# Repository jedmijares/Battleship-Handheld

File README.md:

# Battleship Handheld

This project was created as the final project for EE 287 (Intro to Embedded Systems), by Jed Mijares and Jacob Culler.

## YouTube Video Demo

[Watch Here](https://www.youtube.com/watch?v=jDSAx5fQOlo)

## Compiling

Battleship was written and built with Keil uVision5.

## Description and Operation

If you are not familiar with the board game Battleship, you can read about it [here.](https://en.wikipedia.org/wiki/Battleship_(game))

We implemented the game on a Texas Intrument Tiva C Series Launchpad (EK-TM4C123GXL). When booted up, a short credit message is displayed on a Nokia 5110 screen. The user may press any button to proceed to the game board. The time at which they press the button is used as a seed for a randomization function, and we use this function to randomly place a length 2, length 3, and length 4 ship on an 8x8 grid. Next, the player will use the D-pad to navigate and the select button to fire at the selected square. The game will display an X for each square with a targeted ship and a 0 for each targeted empty square. The game is completed when the player has sunken each ship. At this point, a win screen is displayed, showing the number of shots the player had to fire to complete the game. They player can hit any button to reset the game and play again.

## Explanation of Design Choices

We were attracted to using the Nokia 5110 screen, as Dr. Valvano had provided a library for it as part of his online Embedded Systems course, which we referred to often throughout this semester. We settled upon implementing Battleship after discovering that the Nokia screen flickered a lot when sprites were quickly moved across it.

We used an 8x8 grid for the board as it fit nicely on the Nokia's 48x84 pixel screen. This left enough space for 6 rows of 4 characters, which we used to display the number of shots fired, the number of successful hits, and which ships had been successfully sunk. In software, the board is a 2 dimensional array of _Square_ structs, which keep track of whether a tile has been shot and an ID for the ship that resides there (or lack thereof).

The PCB features several extraneous components. These include a terminal block for breaking out UART pins, an extra unused button, and several rows of jumper pins. These serve no purpose in the current design, but were added in case we decided to implement a feature that would require them.

## Parts List

* TM4C123G LaunchPad Evaluation Kit
* Nokia 5110 Screen Breakout Board
* Piezo Buzzer
* 10kR Resistor (5)
* Pushbutton Switch (5)

### Optional Components

* 330R Resistor (may be used to enable the backlight)
* 4-pin terminal block (breaks out the UART pins, which currently are not used)
* 10kR Resistor (for extra button that currently serves no purpose)
* Pushbutton Switch (extra button that currently serves no purpose)

## Flow Diagram

[Code Flow Diagram](https://github.com/jedmijares/EE-287-Final-Project/blob/master/Media/Code%20Block%20Diagram.pdf)

## Explanation of Major Components

The Tiva board is crucial to the project, and controls all the other components and handles the processing for the game itself.

The Tiva communicates with the Nokia 5110 screen serially and uses it to communicate all visual output.

A piezo buzzer is also implemented. Whenever a button is pressed, the SysTick timer is used to oscillate the buzzer pin for a specified number of milliseconds.

The PCB was designed in Autodesk EAGLE. Relevant design files are in the EAGLE folder.

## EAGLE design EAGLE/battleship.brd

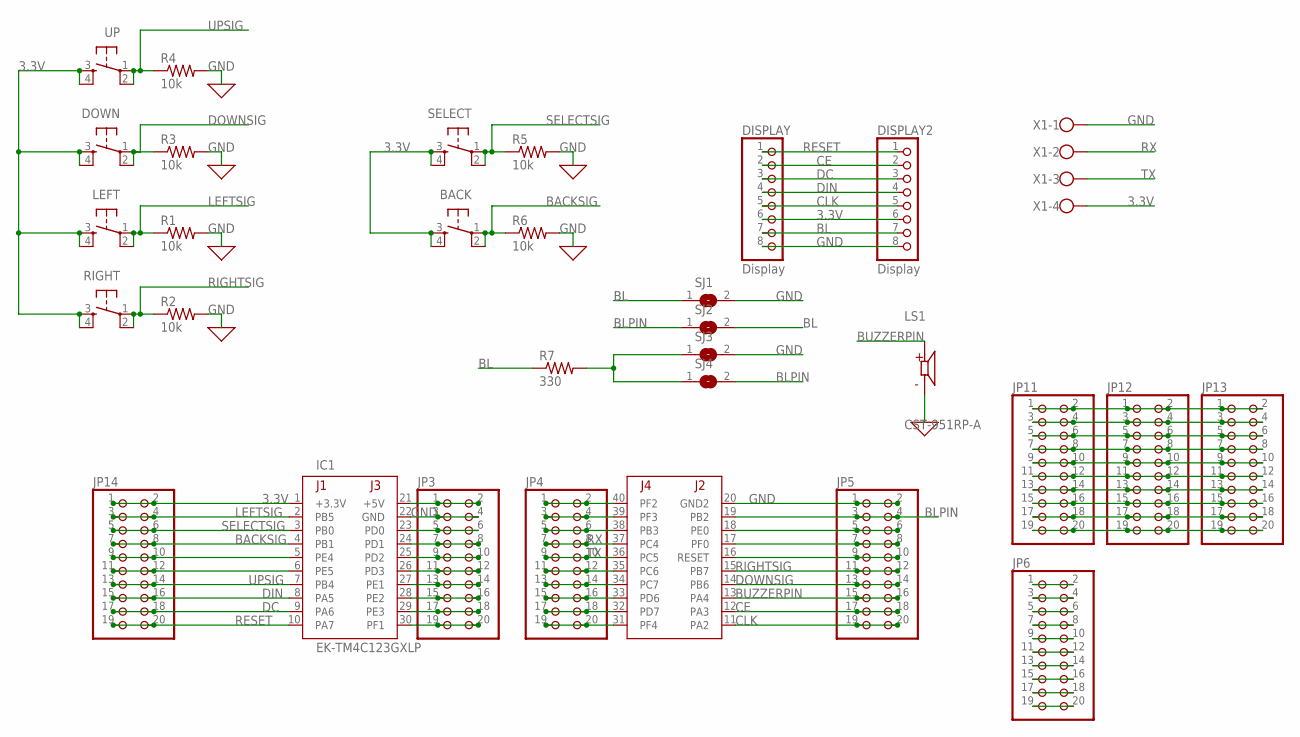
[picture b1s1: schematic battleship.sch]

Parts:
BACK: TAC_SWITCHPTH; TACTILE-PTH
DISPLAY, DISPLAY2: Display; 1X08
DOWN: TAC_SWITCHPTH; TACTILE-PTH
IC1: EK-TM4C123GXLP; TM4C123LAUNCHPAD
JP3, JP4, JP5, JP6, JP11, JP12, JP13, JP14: PINHD-2X10; 2X10
LEFT: TAC_SWITCHPTH; TACTILE-PTH
LS1: CST-951RP-A; CUI_CST-951RP-A
R1, R2, R3, R4, R5, R6: 10k; 0207/10
R7: 330; 0207/10
RIGHT: TAC_SWITCHPTH; TACTILE-PTH
SELECT: TAC_SWITCHPTH; TACTILE-PTH
SJ1, SJ2, SJ3, SJ4: SJ
UP: TAC_SWITCHPTH; TACTILE-PTH
X1: W237-4

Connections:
3.3V: BACK.3, BACK.4, DISPLAY.6, DISPLAY2.6, DOWN.3, DOWN.4, IC1.1 (+3.3V), JP14.1, JP14.2, LEFT.3, LEFT.4, RIGHT.3, RIGHT.4, SELECT.3, SELECT.4, UP.3, UP.4, X1.4
BACKSIG: BACK.1, BACK.2, IC1.4 (PB1), JP14.7, JP14.8, R6.1
BL: DISPLAY.7, DISPLAY2.7, R7.1, SJ1.1, SJ2.2
BLPIN: IC1.19 (PB2), JP5.3, JP5.4, SJ2.1, SJ4.2
BUZZERPIN: IC1.13 (PA4), JP5.15, JP5.16, LS1.P
CE: DISPLAY.2, DISPLAY2.2, IC1.12 (PA3), JP5.17, JP5.18
CLK: DISPLAY.5, DISPLAY2.5, IC1.11 (PA2), JP5.19, JP5.20
DC: DISPLAY.3, DISPLAY2.3, IC1.9 (PA6), JP14.17, JP14.18
DIN: DISPLAY.4, DISPLAY2.4, IC1.8 (PA5), JP14.15, JP14.16
DOWNSIG: DOWN.1, DOWN.2, IC1.14 (PB6), JP5.13, JP5.14, R3.1
GND: DISPLAY.8, DISPLAY2.8, IC1.20 (GND2), IC1.22 (GND), JP3.3, JP3.4, JP5.1, JP5.2, LS1.M, R1.2, R2.2, R3.2, R4.2, R5.2, R6.2, SJ1.2, SJ3.2, X1.1
LEFTSIG: IC1.2 (PB5), JP14.3, JP14.4, LEFT.1, LEFT.2, R1.1
unnamed: JP6.1, JP6.2
unnamed: JP6.3, JP6.4
unnamed: JP6.5, JP6.6
unnamed: JP6.7, JP6.8
unnamed: JP6.9, JP6.10
unnamed: R7.2, SJ3.1, SJ4.1
unnamed: JP6.11, JP6.12
unnamed: JP6.13, JP6.14
unnamed: JP6.15, JP6.16
unnamed: JP6.19, JP6.20
unnamed: JP6.17, JP6.18
unnamed: IC1.5 (PE4), JP14.9, JP14.10
unnamed: IC1.21 (+5V), JP3.1, JP3.2
unnamed: IC1.23 (PD0), JP3.5, JP3.6
unnamed: IC1.24 (PD1), JP3.7, JP3.8
unnamed: IC1.16 (RESET), JP5.9, JP5.10
unnamed: IC1.17 (PF0), JP5.7, JP5.8
unnamed: IC1.18 (PE0), JP5.5, JP5.6
unnamed: IC1.28 (PE2), JP3.15, JP3.16
unnamed: IC1.29 (PE3), JP3.17, JP3.18
unnamed: IC1.30 (PF1), JP3.19, JP3.20
unnamed: IC1.31 (PF4), JP4.19, JP4.20
unnamed: IC1.32 (PD7), JP4.17, JP4.18
unnamed: IC1.26 (PD3), JP3.11, JP3.12
unnamed: IC1.25 (PD2), JP3.9, JP3.10
unnamed: JP11.3, JP11.4, JP12.3, JP12.4, JP13.3, JP13.4
unnamed: JP11.7, JP11.8, JP12.7, JP12.8, JP13.7, JP13.8
unnamed: IC1.33 (PD6), JP4.15, JP4.16
unnamed: IC1.34 (PC7), JP4.13, JP4.14
unnamed: JP11.11, JP11.12, JP12.11, JP12.12, JP13.11, JP13.12
unnamed: IC1.35 (PC6), JP4.11, JP4.12
unnamed: JP11.15, JP11.16, JP12.15, JP12.16, JP13.15, JP13.16
unnamed: JP11.17, JP11.18, JP12.17, JP12.18, JP13.17, JP13.18
unnamed: JP11.19, JP11.20, JP12.19, JP12.20, JP13.19, JP13.20
unnamed: IC1.38 (PB3), JP4.5, JP4.6
unnamed: IC1.39 (PF3), JP4.3, JP4.4
unnamed: IC1.40 (PF2), JP4.1, JP4.2
unnamed: IC1.6 (PE5), JP14.11, JP14.12
unnamed: IC1.27 (PE1), JP3.13, JP3.14
unnamed: JP11.1, JP11.2, JP12.1, JP12.2, JP13.1, JP13.2
unnamed: JP11.5, JP11.6, JP12.5, JP12.6, JP13.5, JP13.6
unnamed: JP11.9, JP11.10, JP12.9, JP12.10, JP13.9, JP13.10
unnamed: JP11.13, JP11.14, JP12.13, JP12.14, JP13.13, JP13.14
RESET: DISPLAY.1, DISPLAY2.1, IC1.10 (PA7), JP14.19, JP14.20
RIGHTSIG: IC1.15 (PB7), JP5.11, JP5.12, R2.1, RIGHT.1, RIGHT.2
RX: IC1.37 (PC4), JP4.7, JP4.8, X1.2
SELECTSIG: IC1.3 (PB0), JP14.5, JP14.6, R5.1, SELECT.1, SELECT.2
TX: IC1.36 (PC5), JP4.9, JP4.10, X1.3
UPSIG: IC1.7 (PB4), JP14.13, JP14.14, R4.1, UP.1, UP.2

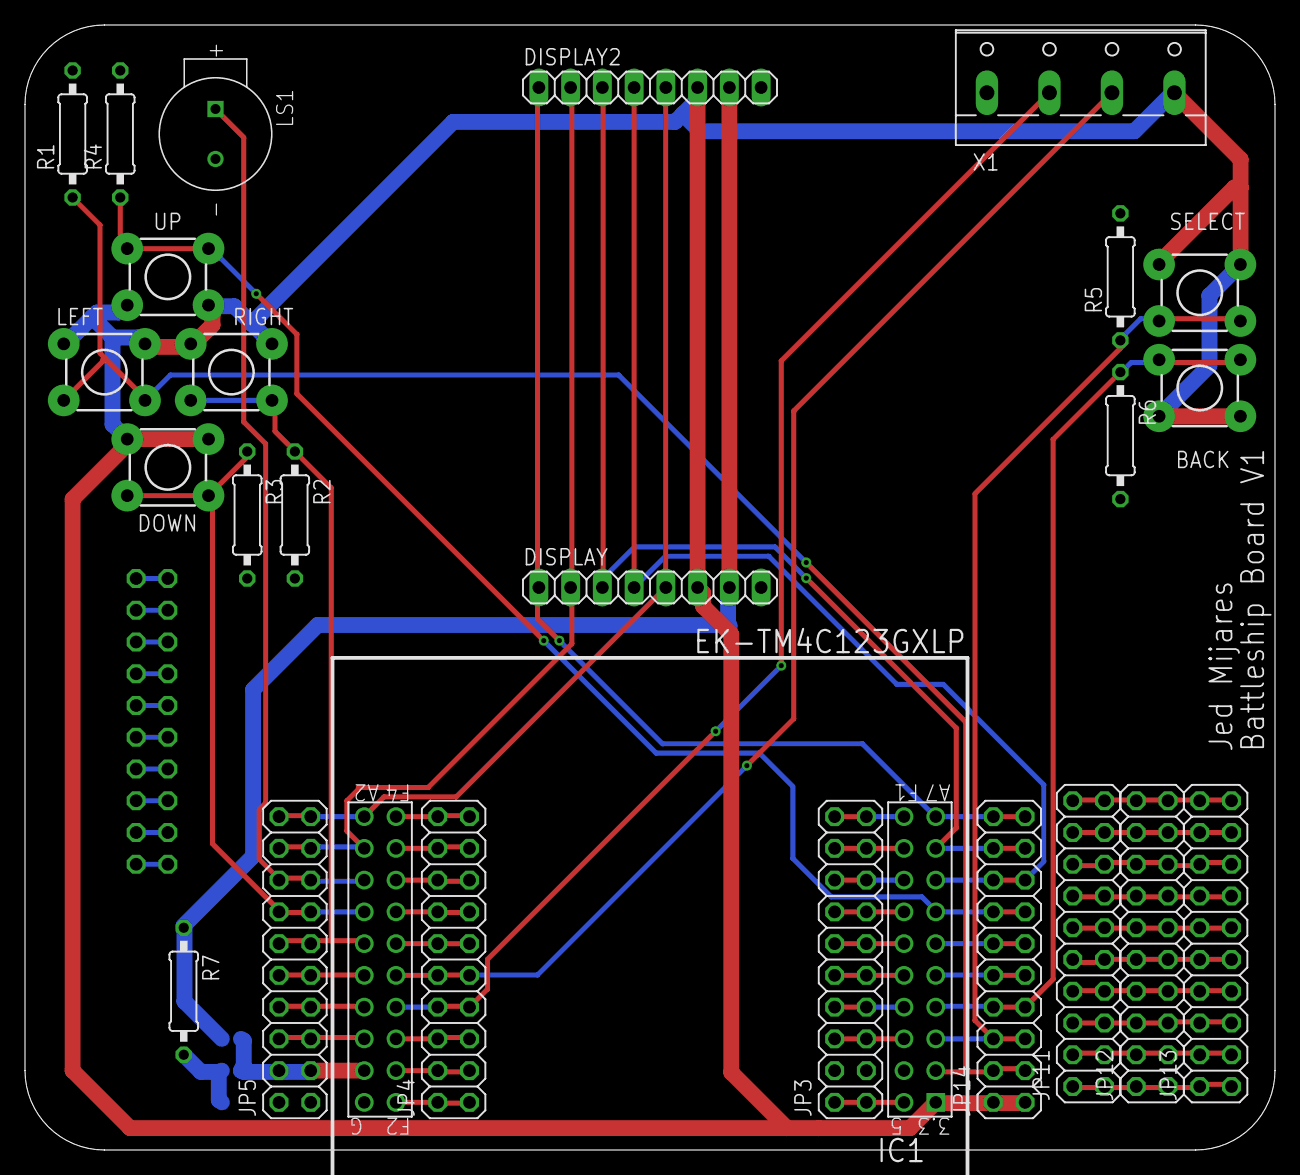
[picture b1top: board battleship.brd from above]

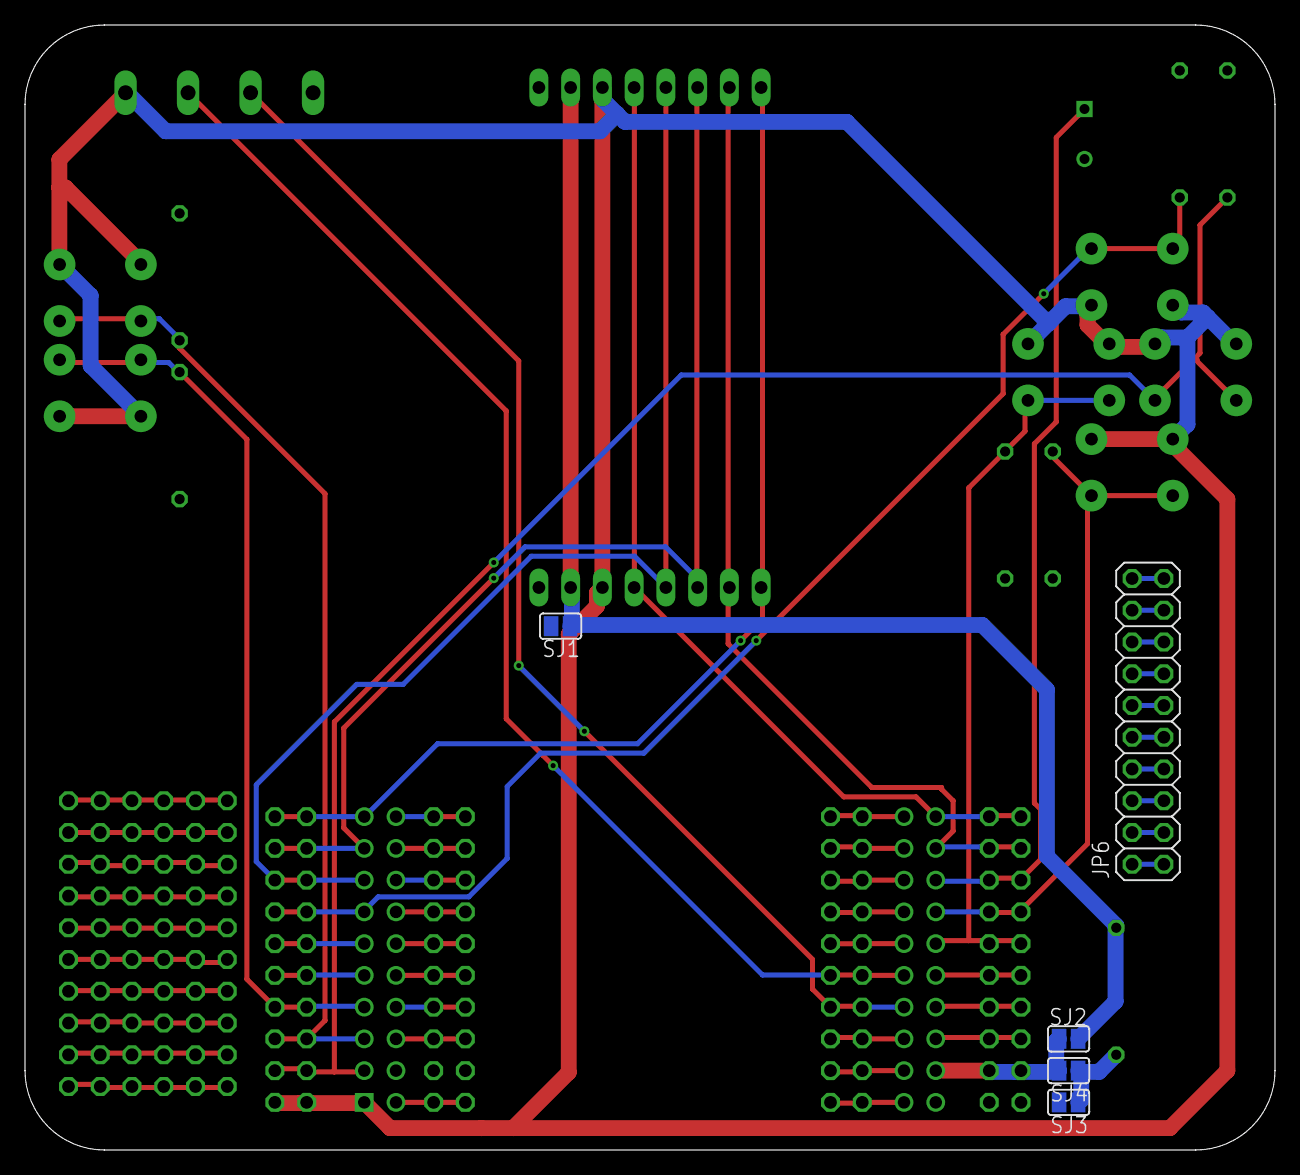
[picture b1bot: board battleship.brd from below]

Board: 2 copper layers, 100.0 x 90.0 mm, 30 parts (5 on the bottom side), 61 nets.

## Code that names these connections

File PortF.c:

#include "PortF.h"
#include "stdint.h"
#include "tm4c123gh6pm.h"


#define PF40 (*((volatile unsigned long *)0x40025044))
#define RLED (*((volatile unsigned long *)0x40025008))
#define GLED (*((volatile unsigned long *)0x40025020))
#define BLED (*((volatile unsigned long *)0x40025010))
#define BUZZER (*((volatile unsigned long *)0x40004040)) // PA4


void Ports_Init(void){
	//Initialize PF3, PF2, and PF1 as outputs
	//Initialize PF4 and PF0 as inputs
	volatile unsigned long delay;
	SYSCTL_RCGC2_R |= 0x00000023;     // 1) A, B, F clock
  delay = SYSCTL_RCGC2_R;           // delay   
  GPIO_PORTF_LOCK_R = 0x4C4F434B;   // 2) unlock PortF PF0  
  GPIO_PORTF_CR_R = 0x1F;           // allow changes to PF4-0 
	
  GPIO_PORTF_AMSEL_R = 0x00;        // 3) disable analog function
	GPIO_PORTA_AMSEL_R = 0x00;        // 3) disable analog function
	GPIO_PORTB_AMSEL_R = 0x00;        // 3) disable analog function
	
  GPIO_PORTF_PCTL_R = 0x00000000;   // 4) GPIO clear bit PCTL  
	GPIO_PORTA_PCTL_R = 0x00000000;   // 4) GPIO clear bit PCTL  
	GPIO_PORTB_PCTL_R = 0x00000000;   // 4) GPIO clear bit PCTL  
	
  GPIO_PORTF_DIR_R = 0x0E;          // 5) PF4,PF0 input, PF3,PF2,PF1 output   
	GPIO_PORTA_DIR_R |= 0x10;         // PA4 out
	GPIO_PORTB_DIR_R &= ~0xF3; 				// B0 1 4 5 6 7 in            
	
  GPIO_PORTF_AFSEL_R = 0x00;        // 6) no alternate function
	GPIO_PORTA_AFSEL_R = 0x00;        // 6) no alternate function
	GPIO_PORTB_AFSEL_R = 0x00;        // 6) no alternate function
	
  GPIO_PORTF_PUR_R = 0x11;          // enable pullup resistors on PF4,PF0    
	
  GPIO_PORTF_DEN_R |= 0x1F;          // 7) enable digital pins PF4-PF0        
	GPIO_PORTA_DEN_R |= 0x10;
	GPIO_PORTB_DEN_R |= 0xF3;
}

void buzzerToggle(void) // toggles A4
{
	BUZZER ^= 0x10;
}

uint32_t pushbuttons(void){
	//Return the state of the PortF buttons
	return(PF40 & 0x11);
}

void blueOn(void){
	BLED |= 0xFF;
}

void redOn(void){
	RLED |= 0xFF;
}

void greenOn(void){
	GLED |= 0xFF;
}

void blueOff(void){
	BLED &= 0x00;
}

void redOff(void){
	RLED &= 0x00;
}

void greenOff(void){
	GLED &= 0x00;
}

void blueToggle(void){
	BLED ^= 0xFF;
}

void redToggle(void){
	RLED ^= 0xFF;
}

void greenToggle(void){
	GLED ^= 0xFF;
}

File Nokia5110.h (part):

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// Blue Nokia 5110
// ---------------
// Signal        (Nokia 5110) LaunchPad pin
// Reset         (RST, pin 1) connected to PA7
// SSI0Fss       (CE,  pin 2) connected to PA3
// Data/Command  (DC,  pin 3) connected to PA6
// SSI0Tx        (Din, pin 4) connected to PA5
// SSI0Clk       (Clk, pin 5) connected to PA2
// 3.3V          (Vcc, pin 6) power
// back light    (BL,  pin 7) not connected, consists of 4 white LEDs which draw ~80mA total
// Ground        (Gnd, pin 8) ground
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// Signal        (Nokia 5110) LaunchPad pin
// 3.3V          (VCC, pin 1) power
// Ground        (GND, pin 2) ground
// SSI0Fss       (SCE, pin 3) connected to PA3
// Reset         (RST, pin 4) connected to PA7
// Data/Command  (D/C, pin 5) connected to PA6
// SSI0Tx        (DN,  pin 6) connected to PA5
// SSI0Clk       (SCLK, pin 7) connected to PA2
// back light    (LED, pin 8) not connected, consists of 4 white LEDs which draw ~80mA total

// Maximum dimensions of the LCD, although the pixels are
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
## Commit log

2019-04-05 lcd and button demo
2019-04-06 implemented SysTick interrupts
2019-04-06 added button debounce demo with SysTick interrupts
2019-04-06 update main
2019-04-06 Update main.c
    move sprite
2019-04-07 testingoutput
2019-04-07 added delay function back
2019-04-07 grid update
2019-04-07 all new sprites
2019-04-07 Revert "Update main.c"
    This reverts commit ba1d74087023149133f328636cbdf123494b8bd7, reversing
    changes made to bf83926d6c4e6ccff65b453e9a03c15814366846.
2019-04-07 Revert "Revert "Update main.c""
    This reverts commit 42dc9f1fc80e100358e0df1b27d34402bff489e0.
2019-04-07 image.h
2019-04-07 fixed main
2019-04-07 added delay to systick header
2019-04-07 initialize sea
2019-04-07 PrintMA
2019-04-07 sprites
2019-04-07 tried to fix stuff
2019-04-07 fixed things
2019-04-07 selector works
    issue was in your code, i<7 means it only hits 6, not 7, the max of a 8x8
2019-04-07 oops
2019-04-07 fixed warnings
2019-04-07 hit worksish
    2 button hit works if you can click both fast enough
2019-04-08 blink and buttons in systick
2019-04-08 added stuff
2019-04-08 got buttons working
2019-04-08 blink work and bounds
2019-04-08 cleaned stuff up
2019-04-08 no matrix
2019-04-08 removed unnecessary stuff
2019-04-08 fix merge error
2019-04-08 works?
2019-04-08 tried to set win condition
2019-04-09 successfully checks win
2019-04-09 added a comment
2019-04-09 added piezo beep
2019-04-09 removed obsolete code
2019-04-09 remove .scvd
2019-04-10 added A and B port init
2019-04-10 renamed port files
2019-04-10 renamed ports files, removed unnecesary code
2019-04-10 added external button functionality
2019-04-10 added tiva pcb library
2019-04-10 added EAGLE files
2019-04-10 edit
2019-04-10 hardware functional
2019-04-10 update EAGLE files
2019-04-10 finished board
2019-04-10 added ground vias
2019-04-10 minor board changes
2019-04-11 edit boards
2019-04-12 reduced PCB size
2019-04-16 added board dxf
2019-04-17 update board and dxf
2019-04-17 add dxf
2019-04-20 added definitions
2019-04-20 added Valvano's random files
2019-04-20 created new version of OutUDec
2019-04-20 cleaned up right text
2019-04-20 renamed struct files, added ship placement
2019-04-20 added ship placement
2019-04-20 added x-y randomization
2019-04-20 added start sequence, time randomize seed
2019-04-22 added more ships
2019-04-22 implemented horizontal/vertical randomization
2019-04-22 try to use bitfields
2019-04-22 added comment
2019-04-23 created media
2019-04-23 minor board updates
2019-04-23 implemented ship ID system and bad win screen
2019-04-23 added an ampersand
2019-04-23 removed sprite.h
2019-04-23 tried to prevent accidental input at start
2019-04-23 adds optional components
2019-04-24 adds block diagram
2019-04-24 added code block diagram
2019-04-24 minor comment
2019-04-24 moved source files into dedicated folder
2019-04-24 Added winscreen and loop
    pretty winscreen and loop back to title on win
2019-04-24 added win screen function to printMatrix.h
2019-04-24 updated win
2019-04-26 got rid of spaces
2019-05-24 adds author names to README

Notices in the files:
Nokia5110.h:
"Embedded Systems: Introduction to ARM Cortex M Microcontrollers",
ISBN: 978-1469998749, Jonathan Valvano, copyright (c) 2014
Copyright 2014 by Jonathan W. Valvano, valvano@mail.utexas.edu
